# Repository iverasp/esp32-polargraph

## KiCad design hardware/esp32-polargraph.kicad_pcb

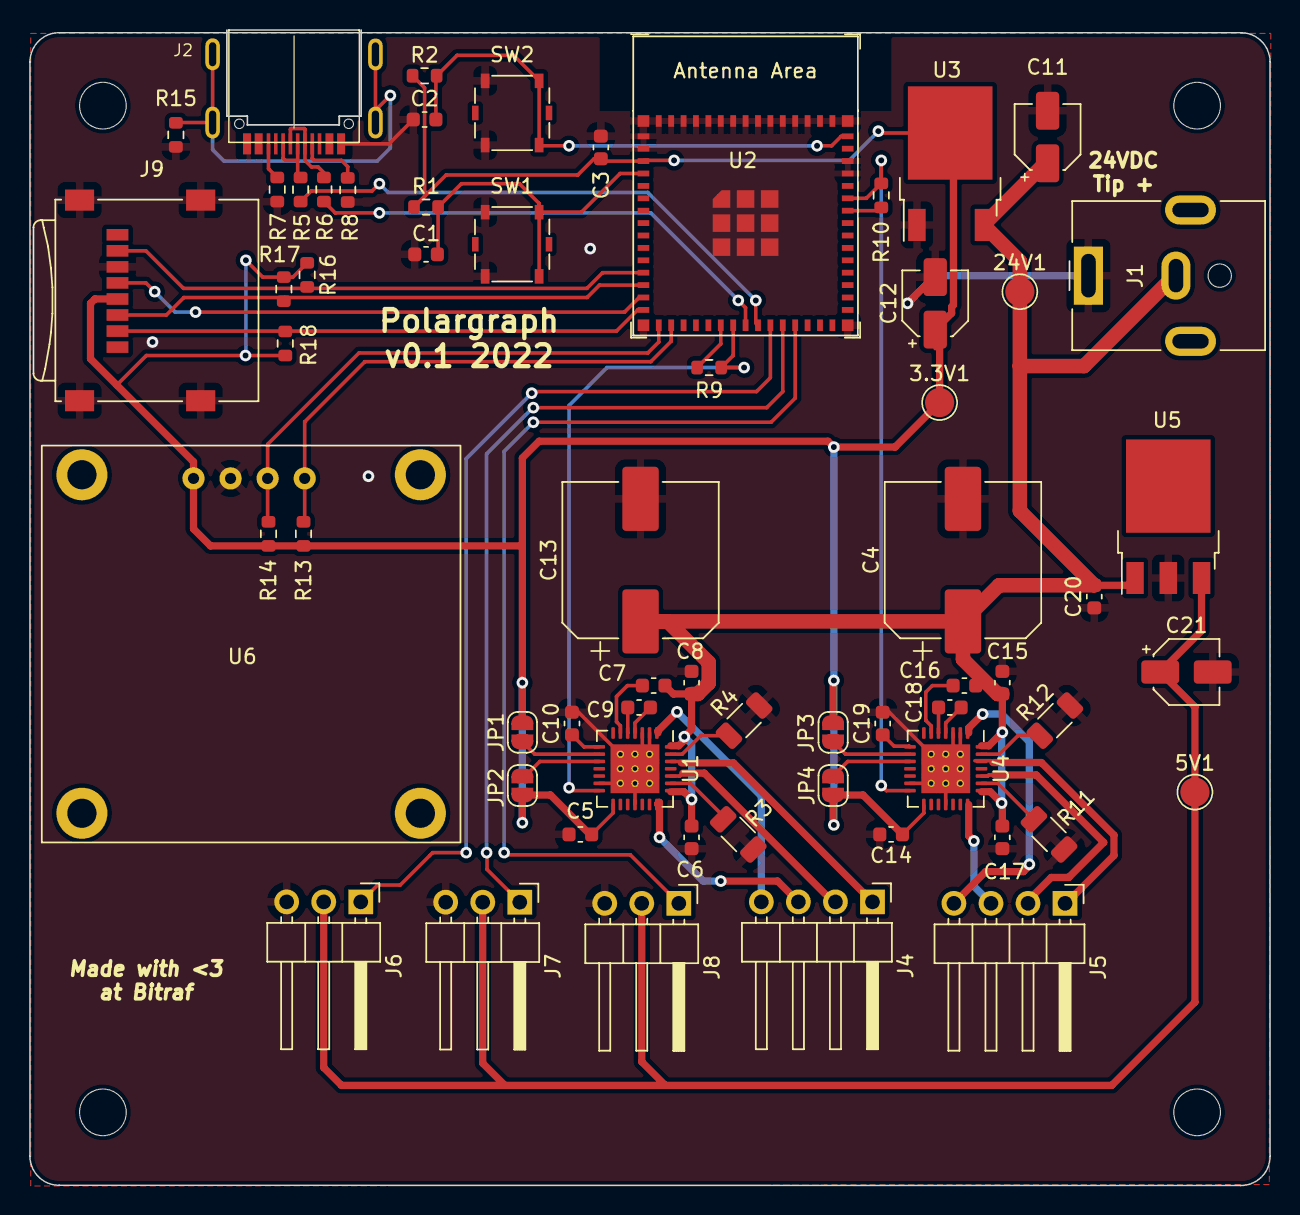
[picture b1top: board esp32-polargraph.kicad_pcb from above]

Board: 2 copper layers, 85.0 x 79.0 mm, 66 parts (0 on the bottom side), 51 nets.

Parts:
3.3V1, 5V1, 24V1: TestPoint; TestPoint_Pad_D2.0mm
C1, C2, C3, C5, C6, C7, C8, C14, C15, C16, C17, C20: 0.1uF; C_0603_1608Metric
C4, C13: 100uF; CP_Elec_10x10.5
C9, C18: 22nF; C_0603_1608Metric
C10, C19: 2.2uF; C_0603_1608Metric
C11, C12: 10uF; CP_Elec_4x5.4
C21: 22uF; CP_Elec_4x5.4
H1, H2, H3, H4: Conn_01x01_Female; MountingHole_3.2mm_M3
J1: 24VDC; BarrelJack_CUI_PJ-063AH_Horizontal
J2: USB_C_Receptacle_USB2.0; TYPE-C-31-M-14
J4: Left motor; PinHeader_1x04_P2.54mm_Horizontal
J5: Right motor; PinHeader_1x04_P2.54mm_Horizontal
J6: Stepper A; PinHeader_1x03_P2.54mm_Horizontal
J7: Stepper B; PinHeader_1x03_P2.54mm_Horizontal
J8: Stepper C; PinHeader_1x03_P2.54mm_Horizontal
J9: Micro_SD_Card; microSD_HC_Wuerth_693072010801
JP1, JP2, JP3, JP4: SolderJumper_2_Open; SolderJumper-2_P1.3mm_Open_RoundedPad1.0x1.5mm
R1, R2, R16, R17, R18: 10k; R_0603_1608Metric
R3, R4, R11, R12: R; R_1206_3216Metric
R5, R6: 33R; R_0603_1608Metric
R7, R8: 5.1k; R_0603_1608Metric
R9, R10: R; R_0603_1608Metric
R13, R14: 4k7; R_0603_1608Metric
R15: 1M; R_0603_1608Metric
SW1: BOOT; SW_SPST_Panasonic_EVQPL_3PL_5PL_PT_A08
SW2: EN; SW_SPST_Panasonic_EVQPL_3PL_5PL_PT_A08
U1, U4: TMC2224-LA-T; QFN-28-1EP_5x5mm_P0.5mm_EP3.35x3.35mm_ThermalVias
U2: ESP32-S3-MINI-1
U3: NCP1117-3.3_SOT223; TO-252-2
U5: NCV4274ADT50RKG; TO-252-3_TabPin4
U6: 0.96_SSD1306

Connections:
+3V3: 3.3V1.1, C3.2, C5.1, C12.1, C14.1, J9.4 (VDD), JP1.1 (A), JP2.1 (A), JP3.1 (A), JP4.1 (A), R1.1, R2.1, R13.2, R14.2, R16.1, R17.1, R18.1, U1.15 (VCC_IO), U2.3 (3V3), U3.2 (VO), U4.15 (VCC_IO), U6.1 (VCC)
+5V: 5V1.1, C21.1, J6.2, J7.2, J8.2, U5.3 (Q)
+24V: 24V1.1, C4.1, C6.1, C7.2, C8.1, C11.1, C13.1, C15.1, C16.2, C17.1, C20.2, J1.2, U1.22 (VS), U1.28 (VS), U3.3 (VI), U4.22 (VS), U4.28 (VS), U5.1 (I)
GND: C1.1, C2.1, C3.1, C4.2, C5.2, C6.2, C8.2, C10.2, C11.2, C12.2, C13.2, C14.2, C15.2, C17.2, C19.2, C20.1, C21.2, J1.1, J2.A1 (GND), J2.A12 (GND), J2.B1 (GND), J2.B12 (GND), J6.3, J7.3, J8.3, J9.6 (VSS), J9.9 (SHIELD), R3.1, R4.1, R7.1, R8.1, R11.1, R12.1, R15.1, SW1.1, SW2.1, U1.2 (ENN), U1.3 (GND), U1.13 (CLK), U1.18 (GND), U1.29 (PAD), U2.1 (GND), U2.2 (GND), U2.42 (GND), U2.43 (GND), U2.46 (GND), U3.1 (GND), U4.2 (ENN), U4.3 (GND), U4.13 (CLK), U4.18 (GND), U4.29 (PAD), U5.2 (GND), U6.2 (GND)
unnamed: C1.2, R1.2, SW1.2, U2.4 (GPIO0/BOOT)
unnamed: C2.2, R2.2, SW2.2, U2.45 (EN)
unnamed: C7.1, U1.6 (VCP)
unnamed: C9.1, U1.5 (CPI)
unnamed: C9.2, U1.4 (CPO)
unnamed: C10.1, U1.8 (5VOUT)
unnamed: C16.1, U4.6 (VCP)
unnamed: C18.1, U4.5 (CPI)
unnamed: C18.2, U4.4 (CPO)
unnamed: C19.1, U4.8 (5VOUT)
unnamed: J2.A4 (VBUS), J2.A9 (VBUS), J2.B4 (VBUS), J2.B9 (VBUS)
unnamed: J2.A5 (CC1), R8.2
unnamed: J2.A6 (D+), J2.B6 (D+), R5.2
unnamed: J2.A7 (D-), J2.B7 (D-), R6.2
unnamed: J2.B5 (CC2), R7.2
unnamed: J2.S1 (SHIELD), R15.2
unnamed: J4.1, U1.26 (OB1)
unnamed: J4.2, U1.24 (OA1)
unnamed: J4.3, U1.21 (OA2)
unnamed: J4.4, U1.1 (OB2)
unnamed: J5.1, U4.26 (OB1)
unnamed: J5.2, U4.24 (OA1)
unnamed: J5.3, U4.21 (OA2)
unnamed: J5.4, U4.1 (OB2)
unnamed: JP1.2 (B), U1.9 (MS1)
unnamed: JP2.2 (B), U1.10 (MS2)
unnamed: JP3.2 (B), U4.9 (MS1)
unnamed: JP4.2 (B), U4.10 (MS2)
unnamed: R3.2, U1.23 (BRA)
unnamed: R4.2, U1.27 (BRB)
unnamed: R5.1, U2.24 (GPIO20/U1CTS/ADC2_CH9/CLK_OUT1/USB_D+)
unnamed: R6.1, U2.23 (GPIO19/U1RTS/ADC2_CH8/CLK_OUT2/USB_D-)
unnamed: R9.1, U2.21 (GPIO17/U1TXD/ADC2_CH6)
unnamed: R9.2, U1.14 (PDN_UART), U2.22 (GPIO18/U1RXD/ADC2_CH7/CLK_OUT3)
unnamed: R10.1, U2.39 (U0TXD/GPIO43/CLK_OUT1)
unnamed: R10.2, U2.40 (U0RXD/GPIO44/CLK_OUT2), U4.14 (PDN_UART)
unnamed: R11.2, U4.23 (BRA)
unnamed: R12.2, U4.27 (BRB)
unnamed: R13.1, U2.17 (GPIO13/TOUCH13/ADC2_CH2/FSPIQ/FSPIIO7/S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), U6.4 (SDA)
unnamed: R14.1, U2.16 (GPIO12/TOUCH11/ADC2_CH0/FSPICS0/FSPIIO4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), U6.3 (SCL)
SPI_CLK: J9.5 (CLK), U2.14 (GPIO10/TOUCH10/ADC1_CH9/FSPICS0/FSPIIO4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)
SPI_CS: J9.2 (DAT3/CD), R18.2, U2.15 (GPIO11/TOUCH11/ADC2_CH0/FSPICS0/FSPIIO4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)
SPI_MISO: J9.7 (DAT0), R16.2, U2.12 (GPIO8/TOUCH8/ADC1_CH7/SUBSPICS1)
SPI_MOSI: J9.3 (CMD), R17.2, U2.13 (GPIO9/TOUCH9/ADC1_CH8/FSPIHD/SUBSPIHD)
Stepper A: J6.1, U2.25 (GPIO21)
Stepper B: J7.1, U2.26 (GPIO26)
Stepper C: J8.1, U2.27 (GPIO47/SPICLK_P/SUBSPICLK_P_DIFF)

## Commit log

2022-03-22 Almost finished pcb
2022-03-22 Beginning on enclosure
